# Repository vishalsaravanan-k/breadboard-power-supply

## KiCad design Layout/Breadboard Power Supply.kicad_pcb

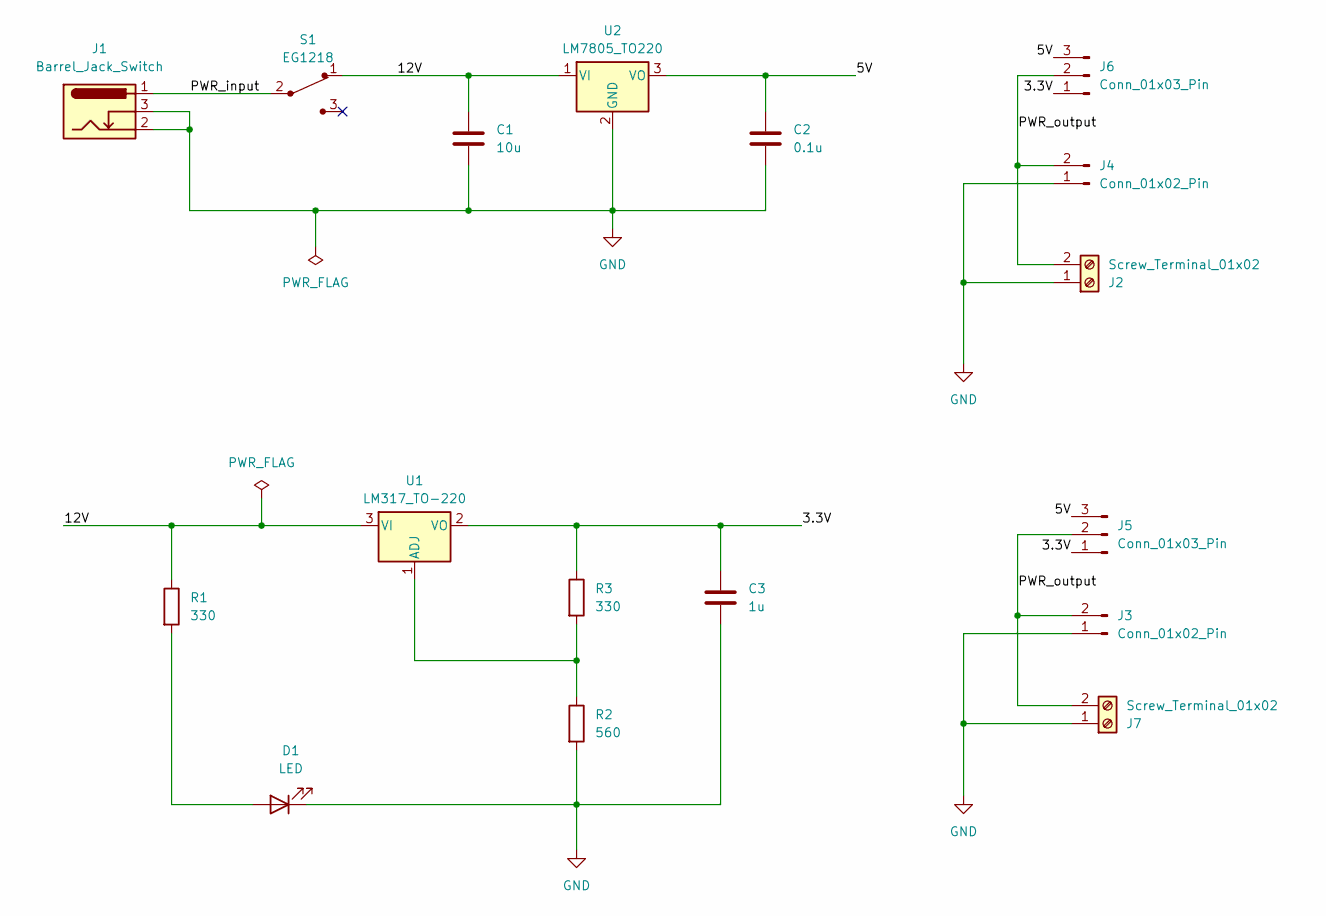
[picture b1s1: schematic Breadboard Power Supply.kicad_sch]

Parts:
C1: 10u; C_Radial_D4.0mm_H5.0mm_P1.50mm
C2: 0.1u; C_Disc_D3.0mm_W1.6mm_P2.50mm
C3: 1u; C_Disc_D3.4mm_W2.1mm_P2.50mm
D1: LED; LED_D4.0mm
J1: Barrel_Jack_Switch; BarrelJack_Horizontal
J2, J7: Screw_Terminal_01x02; TerminalBlock_MaiXu_MX126-5.0-02P_1x02_P5.00mm
J3, J4: Conn_01x02_Pin; PinHeader_1x02_P1.27mm_Vertical
J5, J6: Conn_01x03_Pin; PinHeader_1x03_P1.27mm_Vertical
R1, R3: 330; R_Axial_DIN0204_L3.6mm_D1.6mm_P7.62mm_Horizontal
R2: 560; R_Axial_DIN0204_L3.6mm_D1.6mm_P7.62mm_Horizontal
S1: EG1218; Switch_Slide_11.6x4mm_EG1218; MPN EG1218; Digi-Key_PN EG1903-ND
U1: LM317_TO-220; TO-220-3_Vertical
U2: LM7805_TO220; TO-220-3_Vertical

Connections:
/3.3V: C3.1, J5.1, J6.1, R3.1, U1.2 (VO)
/5V: C2.1, J5.3, J6.3, U2.3 (VO)
/12V: C1.1, R1.1, S1.1, U1.3 (VI), U2.1 (VI)
/PWR_input: J1.1, S1.2
/PWR_output: J2.2, J3.2, J4.2, J5.2, J6.2, J7.2
GND: C1.2, C2.2, C3.2, D1.1 (K), J1.2, J1.3, J2.1, J3.1, J4.1, J7.1, R2.2, U2.2 (GND)
unnamed: D1.2 (A), R1.2
unnamed: R2.1, R3.2, U1.1 (ADJ)

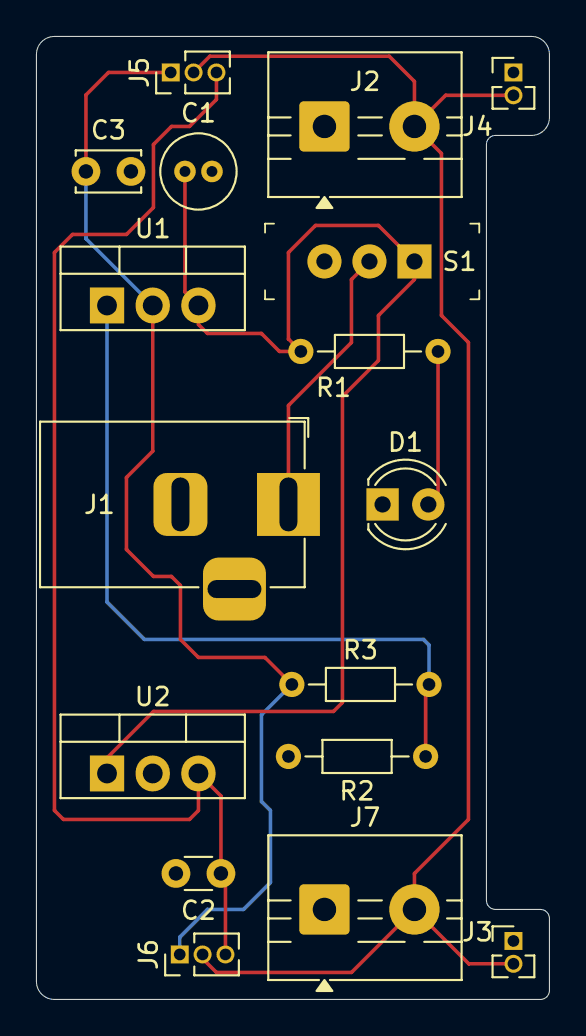
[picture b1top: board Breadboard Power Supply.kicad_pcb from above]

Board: 2 copper layers, 28.5 x 53.5 mm, 17 parts (0 on the bottom side), 8 nets.

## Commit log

2025-05-13 Breadboard Power Supply project
2025-05-13 Second commit: Breadboard Power Supply project Images uploaded
